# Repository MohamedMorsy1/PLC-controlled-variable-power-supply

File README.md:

# PLC-controlled-variable-power-supply

The project is designed on KiCad

It is 2 chennel variable power supply thet can be controlled by a low current analog signal comming from PLC 

the main component is XL4005E

and the feedback is connected to the following circuit

you can find the KiCad project

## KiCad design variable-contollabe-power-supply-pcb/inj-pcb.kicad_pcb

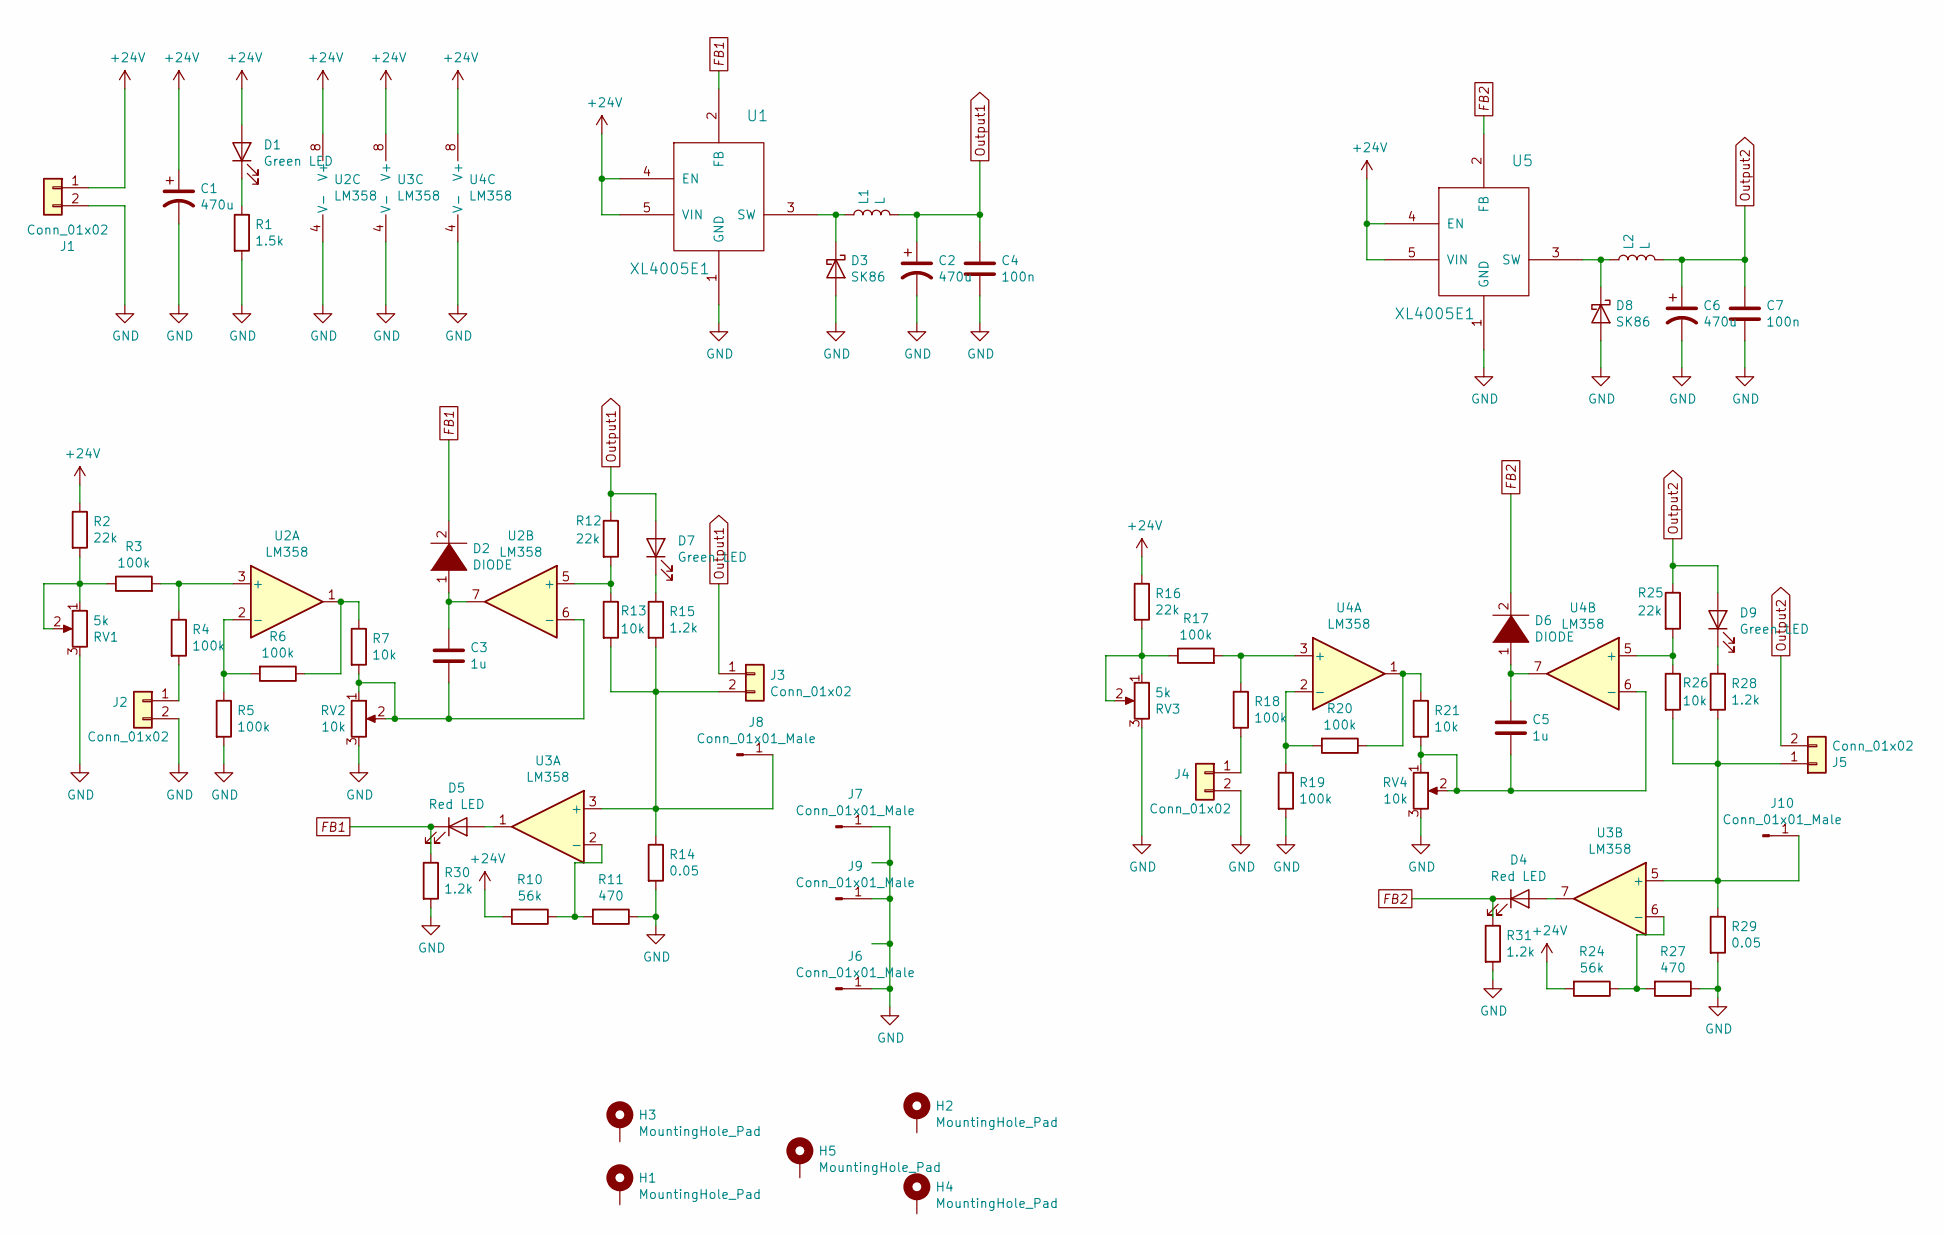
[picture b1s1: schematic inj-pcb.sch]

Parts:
C1, C2, C6: 470u; CP_Elec_10x10
C3, C5: 1u; C_1210_3225Metric_Pad1.42x2.65mm_HandSolder
C4, C7: 100n; C_1210_3225Metric_Pad1.42x2.65mm_HandSolder
D1, D7, D9: Green LED; LED_D3.0mm
D2, D6: DIODE; D_SOD-123F
D3, D8: SK86; D_SMC_Handsoldering
D4, D5: Red LED; LED_D3.0mm
H1, H2, H3, H4, H5: MountingHole_Pad; MountingHole_3.2mm_M3_DIN965_Pad
J1, J2, J3, J4, J5: Conn_01x02; PhoenixContact_MSTBVA_2,5_2-G-5,08_1x02_P5.08mm_Vertical
J6, J7, J8, J9, J10: Conn_01x01_Male; Pin_D1.4mm_L8.5mm_W2.8mm_FlatFork
L1, L2: L; L_Axial_L26.7mm_D12.1mm_P35.00mm_Horizontal_Vishay_IHA-103
R1: 1.5k; R_Axial_DIN0207_L6.3mm_D2.5mm_P10.16mm_Horizontal
R2, R16: 22k; R_Axial_DIN0207_L6.3mm_D2.5mm_P10.16mm_Horizontal
R3, R4, R5, R6, R17, R18, R19, R20: 100k; R_1206_3216Metric_Pad1.42x1.75mm_HandSolder
R7, R21: 10k; R_Axial_DIN0207_L6.3mm_D2.5mm_P10.16mm_Horizontal
R10, R24: 56k; R_1206_3216Metric_Pad1.42x1.75mm_HandSolder
R11, R27: 470; R_1206_3216Metric_Pad1.42x1.75mm_HandSolder
R12, R25: 22k; R_1206_3216Metric_Pad1.42x1.75mm_HandSolder
R13, R26: 10k; R_1206_3216Metric_Pad1.42x1.75mm_HandSolder
R14, R29: 0.05; R_4020_10251Metric_Pad1.65x5.30mm_HandSolder
R15, R28, R30, R31: 1.2k; R_Axial_DIN0207_L6.3mm_D2.5mm_P10.16mm_Horizontal
RV1, RV3: 5k; Potentiometer_Bourns_3296W_Vertical
RV2, RV4: 10k; Potentiometer_Bourns_3296W_Vertical
U1, U5: XL4005E1; TO-263-5_TabPin3
U2, U3, U4: LM358; SO-8_3.9x4.9mm_P1.27mm

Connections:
+24V: C1.1, D1.2 (A), J1.1, R2.1, R10.2, R16.1, R24.2, U1.4 (EN), U1.5 (VIN), U2.8 (V+), U3.8 (V+), U4.8 (V+), U5.4 (EN), U5.5 (VIN)
FB1: D2.2 (A), D5.1 (K), R30.1, U1.2 (FB)
FB2: D4.1 (K), D6.2 (A), R31.1, U5.2 (FB)
GND: C1.2, C2.2, C4.2, C6.2, C7.2, D3.2 (A), D8.2 (A), J1.2, J2.2, J4.2, J6.1, J7.1, J9.1, R1.2, R5.2, R11.1, R14.2, R19.2, R27.1, R29.2, R30.2, R31.2, RV1.3, RV2.3, RV3.3, RV4.3, U1.1 (GND), U2.4 (V-), U3.4 (V-), U4.4 (V-), U5.1 (GND)
unnamed: C3.1, D2.1 (K), U2.7
unnamed: C3.2, R7.2, RV2.1, RV2.2, U2.6 (-)
unnamed: C5.1, D6.1 (K), U4.7
unnamed: C5.2, R21.2, RV4.1, RV4.2, U4.6 (-)
unnamed: D1.1 (K), R1.1
unnamed: D3.1 (K), L1.1, U1.3 (SW)
unnamed: D4.2 (A), U3.7
unnamed: D5.2 (A), U3.1
unnamed: D7.1 (K), R15.1
unnamed: D8.1 (K), L2.1, U5.3 (SW)
unnamed: D9.1 (K), R28.1
unnamed: J2.1, R4.2
unnamed: J3.2, J8.1, R13.2, R14.1, R15.2, U3.3 (+)
unnamed: J4.1, R18.2
unnamed: J5.1, J10.1, R26.2, R28.2, R29.1, U3.5 (+)
unnamed: R2.2, R3.1, RV1.1, RV1.2
unnamed: R3.2, R4.1, U2.3 (+)
unnamed: R5.1, R6.2, U2.2 (-)
unnamed: R6.1, R7.1, U2.1
unnamed: R10.1, R11.2, U3.2 (-)
unnamed: R12.2, R13.1, U2.5 (+)
unnamed: R16.2, R17.1, RV3.1, RV3.2
unnamed: R17.2, R18.1, U4.3 (+)
unnamed: R19.1, R20.2, U4.2 (-)
unnamed: R20.1, R21.1, U4.1
unnamed: R24.1, R27.2, U3.6 (-)
unnamed: R25.2, R26.1, U4.5 (+)
Output1: C2.1, C4.1, D7.2 (A), J3.1, L1.2, R12.1
Output2: C6.1, C7.1, D9.2 (A), J5.2, L2.2, R25.1

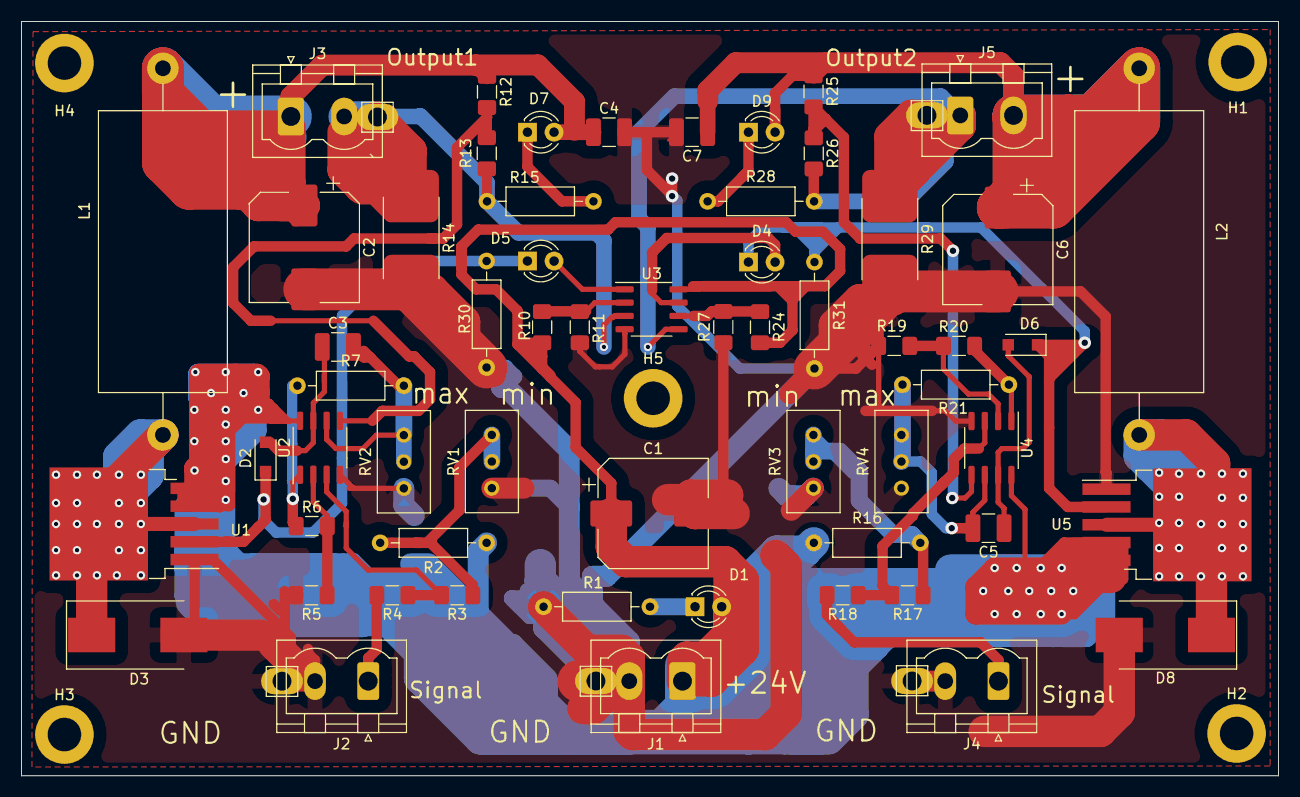
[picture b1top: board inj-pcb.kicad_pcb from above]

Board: 2 copper layers, 120.0 x 72.0 mm, 69 parts (0 on the bottom side), 33 nets.
